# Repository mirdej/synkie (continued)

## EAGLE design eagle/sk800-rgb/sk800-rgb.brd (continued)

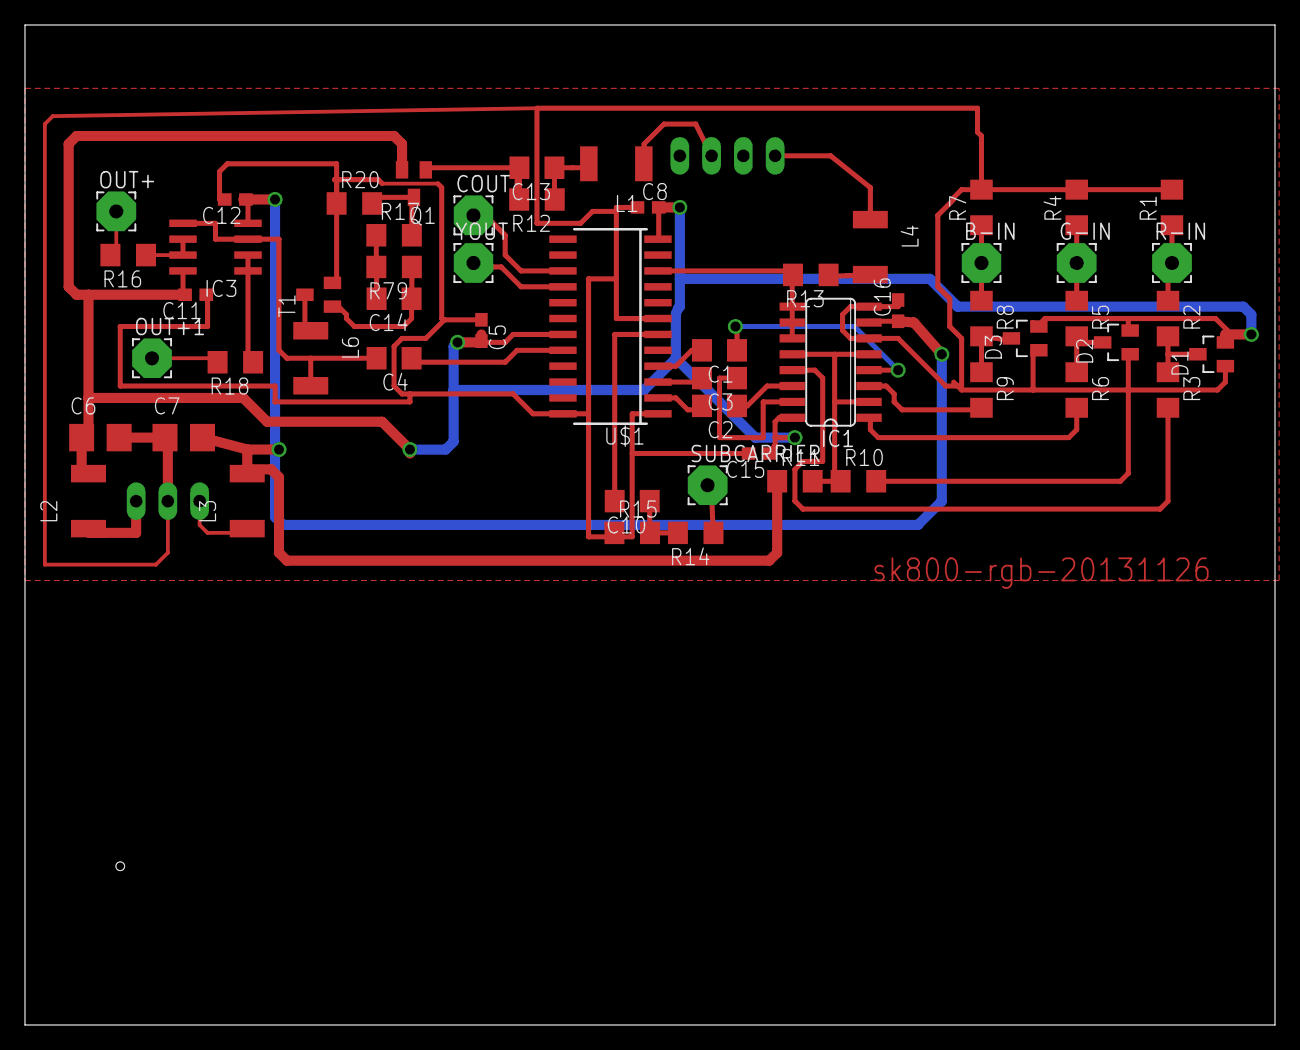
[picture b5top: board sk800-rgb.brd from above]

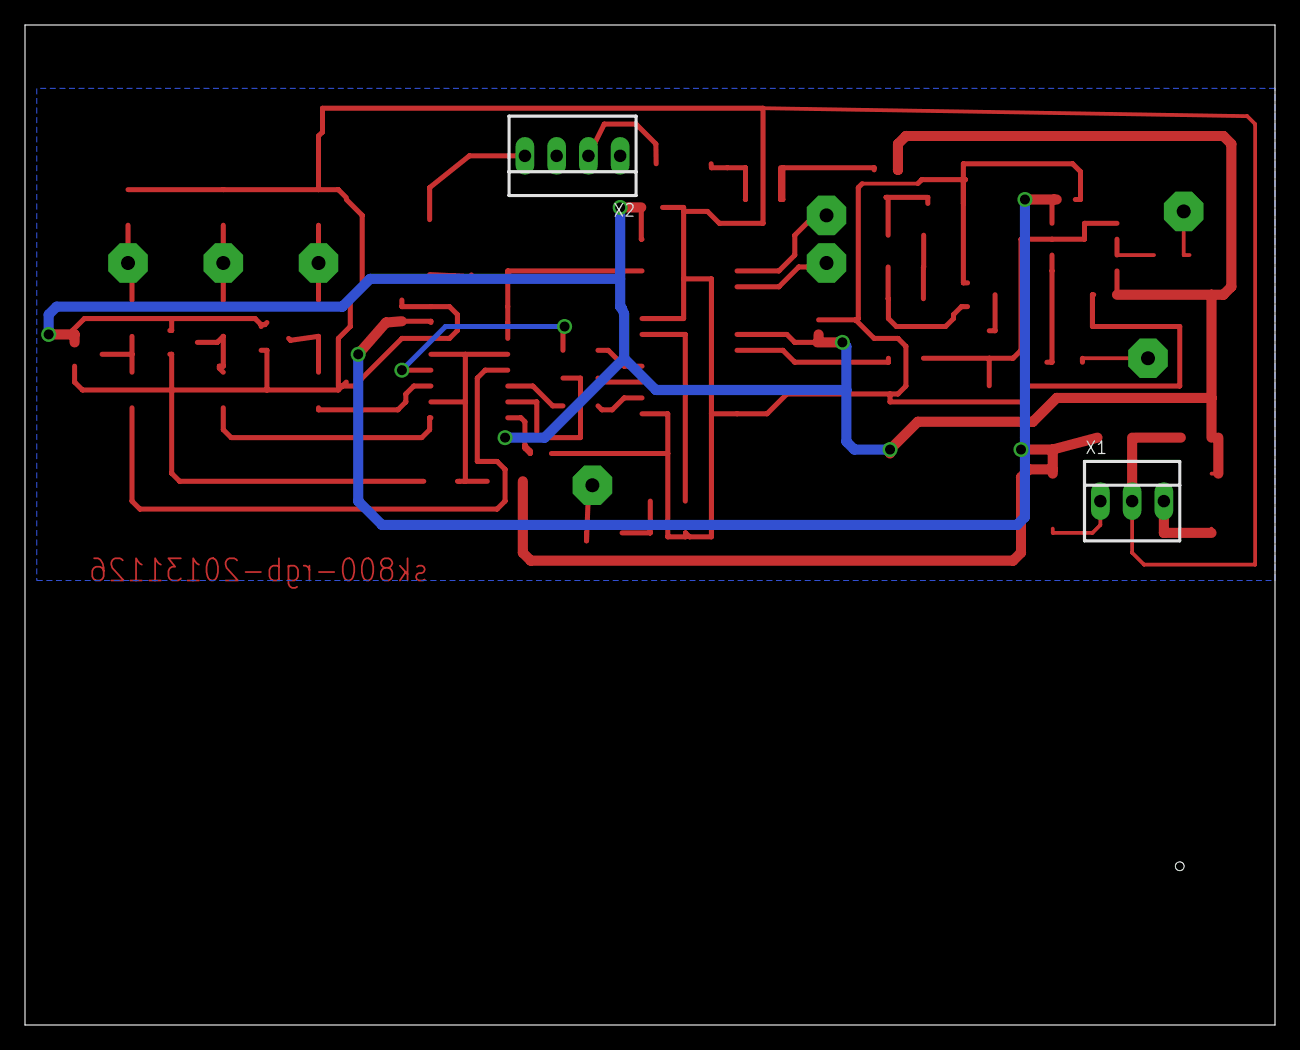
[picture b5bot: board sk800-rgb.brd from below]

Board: 2 copper layers, 100.0 x 80.0 mm, 58 parts (2 on the bottom side), 42 nets.

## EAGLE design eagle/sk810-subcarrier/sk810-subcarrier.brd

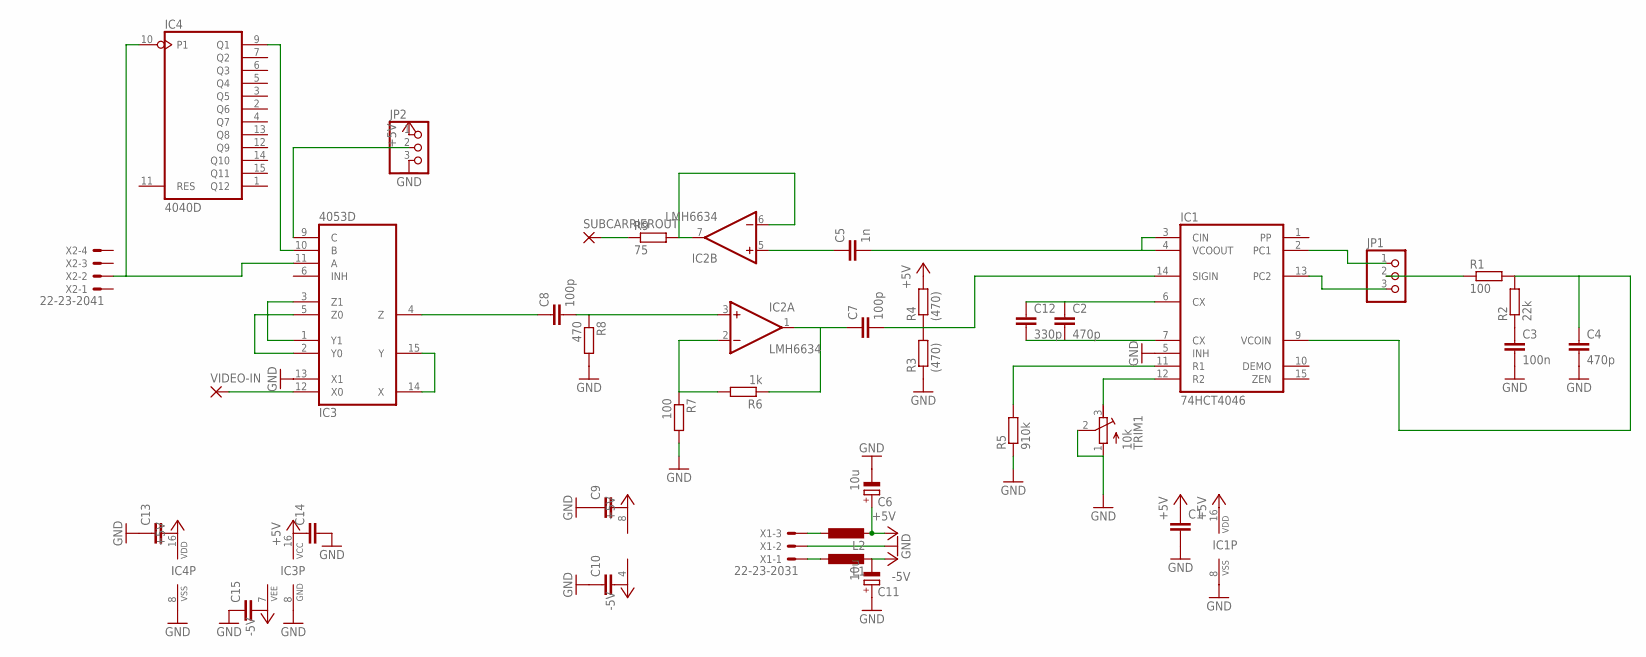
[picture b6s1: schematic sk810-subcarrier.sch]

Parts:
C1, C9, C10: C-EUC0603; C0603
C2, C4: 470p; C1206
C3: 100n; C1206
C5: 1n; C1206
C6, C11: 10u; CT3528
C7, C8: 100p; C1206
C12: 330p; C1206
C13, C14, C15: C-EUC1206; C1206
IC1: 74HCT4046; SO16
IC2: LMH6634; SO08
IC3: 4053D; SO16
IC4: 4040D; SO16
JP1, JP2: PINHD-1X3; 1X03
L1, L2: L-EUL5038P; L5038P
R1, R7: 100; R1206
R2: 22k; R1206
R3, R4: (470); R1206
R5: 910k; R1206
R6: 1k; R1206
R8: 470; R1206
R9: 75; R1206
SUBCARRIEROUT: 3,17/1,1
TRIM1: 10k; RTRIM64Y
VIDEO-IN: 3,17/1,1
X1: 22-23-2031
X2: 22-23-2041

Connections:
+5V: C1.1, C6.+, C9.2, C13.2, C14.1, IC1.16 (VDD), IC2.8 (V+), IC3.16 (VCC), IC4.16 (VDD), JP2.1, L2.2, R4.2
-5V: C10.2, C11.-, C15.2, IC2.4 (V-), IC3.7 (VEE), L1.2
GND: C1.2, C3.2, C4.2, C6.-, C9.1, C10.1, C11.+, C13.1, C14.2, C15.1, IC1.5 (INH), IC1.8 (VSS), IC3.8 (GND), IC3.13 (X1), IC4.8 (VSS), JP2.3, R3.1, R5.1, R7.2, R8.2, TRIM1.1 (E), TRIM1.2 (S), X1.2
unnamed: C2.1, C12.1, IC1.6 (CX)
unnamed: C2.2, C12.2, IC1.7 (CX)
unnamed: IC1.11 (R1), R5.2
unnamed: IC1.12 (R2), TRIM1.3 (A)
unnamed: IC1.2 (PC1), JP1.1
unnamed: IC1.13 (PC2), JP1.3
unnamed: JP1.2, R1.1
unnamed: C4.1, IC1.9 (VCOIN), R1.2, R2.2
unnamed: C3.1, R2.1
unnamed: C5.2, IC1.3 (CIN), IC1.4 (VCOOUT)
unnamed: L2.1, X1.3
unnamed: C5.1, IC2.5 (+IN)
unnamed: IC3.14 (X), IC3.15 (Y)
unnamed: C8.2, IC2.3 (+IN), R8.1
unnamed: IC2.2 (-IN), R6.2, R7.1
unnamed: C7.2, IC1.14 (SIGIN), R3.2, R4.1
unnamed: C7.1, IC2.1 (OUT), R6.1
unnamed: IC2.6 (-IN), IC2.7 (OUT), R9.2
unnamed: R9.1, SUBCARRIEROUT.1
unnamed: L1.1, X1.1
unnamed: IC3.11 (A), IC4.10 (P1), X2.2
unnamed: IC3.12 (X0), VIDEO-IN.1
unnamed: IC3.2 (Y0), IC3.5 (Z0)
unnamed: IC3.1 (Y1), IC3.3 (Z1)
unnamed: C8.1, IC3.4 (Z)
unnamed: IC3.10 (B), IC4.9 (Q1)
unnamed: IC3.9 (C), JP2.2

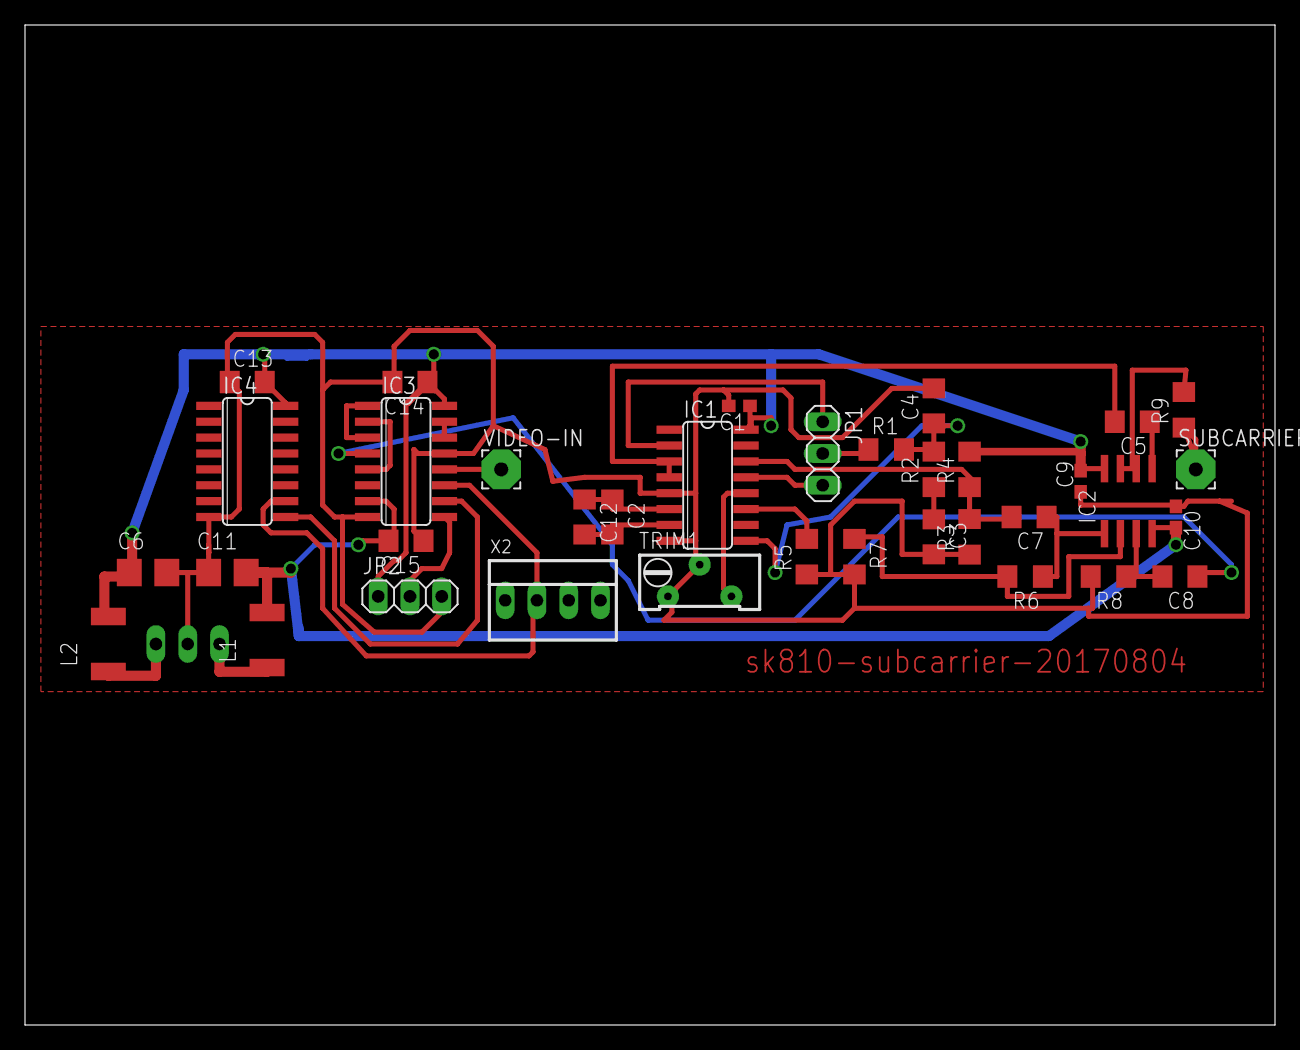
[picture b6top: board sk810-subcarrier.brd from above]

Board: 2 copper layers, 100.0 x 80.0 mm, 37 parts (1 on the bottom side), 30 nets.

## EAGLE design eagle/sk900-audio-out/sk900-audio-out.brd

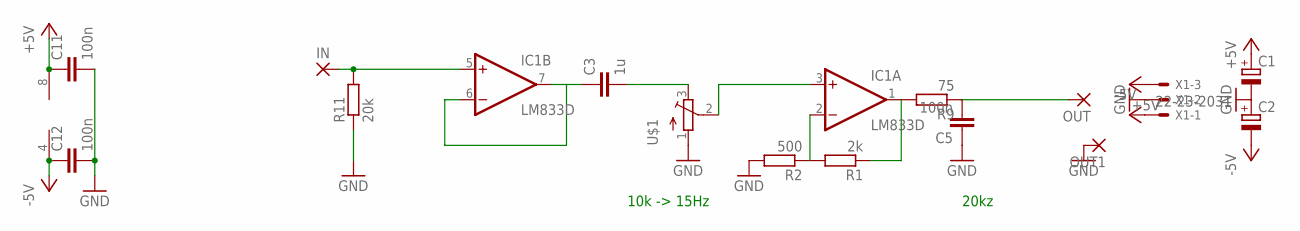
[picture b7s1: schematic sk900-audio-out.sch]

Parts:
C1, C2: CPOL-EUCT6032; CT6032
C3: 1u; C1206
C5, C11, C12: 100n; C1206
IC1: LM833D; SO08
IN: 3,17/1,1
OUT, OUT1: 3,17/1,1
R1: 2k; R1206
R2: 500; R1206
R9: 75; R1206
R11: 20k; R1206
U$1: 10k; ALPS_RK09K111_H
X1: 22-23-2031

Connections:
+5V: C1.+, C11.1, IC1.8 (V+), X1.3
-5V: C2.-, C12.1, IC1.4 (V-), X1.1
GND: C1.-, C2.+, C5.1, C11.2, C12.2, OUT1.1, R2.2, R11.1, U$1.1 (S), X1.2
unnamed: IC1.5 (+IN), IN.1, R11.2
unnamed: C3.2, U$1.3 (E)
unnamed: C3.1, IC1.6 (-IN), IC1.7 (OUT)
unnamed: IC1.3 (+IN), U$1.2 (W)
unnamed: IC1.1 (OUT), R1.1, R9.2
unnamed: C5.2, OUT.1, R9.1
unnamed: IC1.2 (-IN), R1.2, R2.1

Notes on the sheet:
10k -> 15Hz
20kz

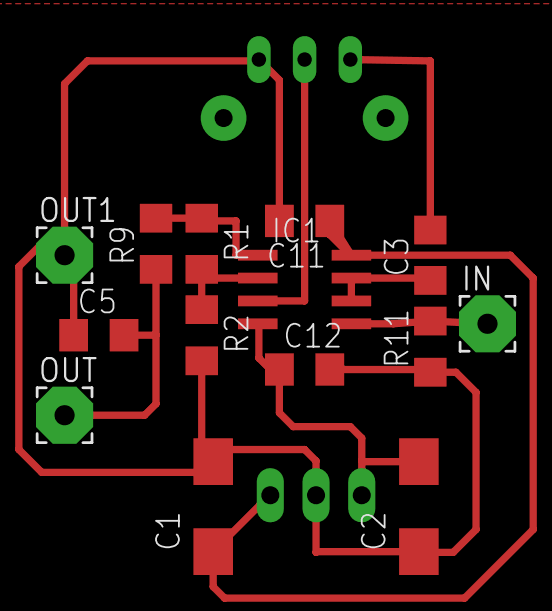
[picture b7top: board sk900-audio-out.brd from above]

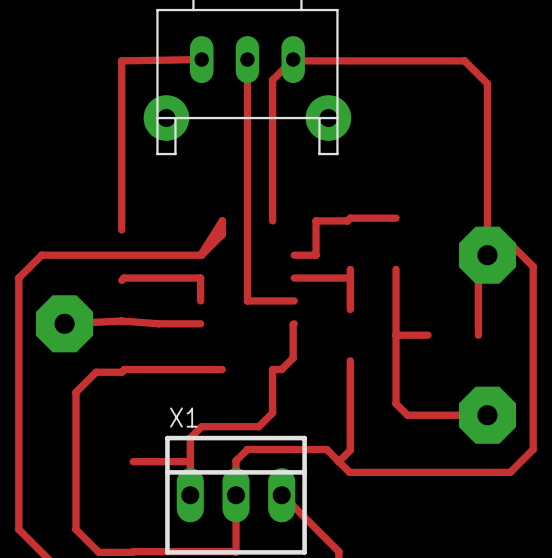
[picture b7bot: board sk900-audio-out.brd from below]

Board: 2 copper layers, 16 parts (2 on the bottom side), 10 nets.
